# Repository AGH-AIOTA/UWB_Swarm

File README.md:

# UWB Swarm
###### Status - Aktywny
Rój autonomicznych pojazdów na bazie podwozia miabotów, które mogą lokalizować się wzajemnie za pomocą modułów [UWB](https://en.wikipedia.org/wiki/Ultra-wideband).
Projekt realizowany jest w ramach grantu [IDUB](https://www.idub.agh.edu.pl/).

_Niech żyje rój!_

### Założenia/Cel
Wykonanie pojazdów mogących lokalizować się wzajemnie i wykonywać czynności autonomicznie.

### Koordynator
**Wiktor Onik**

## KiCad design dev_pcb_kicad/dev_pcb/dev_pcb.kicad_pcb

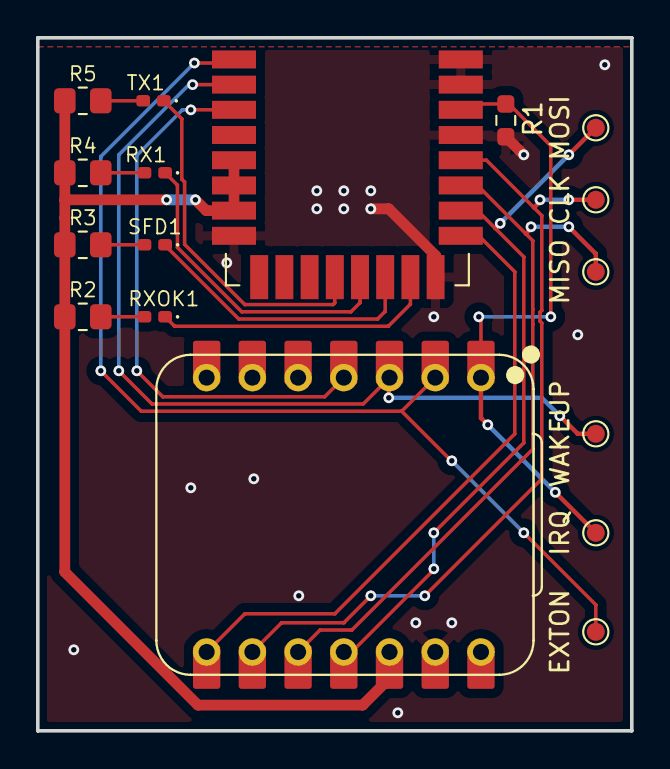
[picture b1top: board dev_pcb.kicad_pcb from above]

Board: 2 copper layers, 33.0 x 38.5 mm, 17 parts (0 on the bottom side), 18 nets.

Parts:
CLK: MISO; TestPoint_Pad_D1.0mm
DWM1: DWM3000; DWM1000
EXTON: TestPoint_Probe; TestPoint_Pad_D1.0mm
IRQ: TestPoint_Probe; TestPoint_Pad_D1.0mm
MISO: CLK; TestPoint_Pad_D1.0mm
MOSI: MOSI; TestPoint_Pad_D1.0mm
R1: 100K; R_0603_1608Metric_Pad0.98x0.95mm_HandSolder
R2, R3, R4, R5: 200; R_0805_2012Metric_Pad1.20x1.40mm_HandSolder
RX1: LED; LED_0402_1005Metric_Pad0.77x0.64mm_HandSolder
RXOK1: LED; LED_0402_1005Metric_Pad0.77x0.64mm_HandSolder
SFD1: LED; LED_0402_1005Metric_Pad0.77x0.64mm_HandSolder
TX1: LED; LED_0402_1005Metric_Pad0.77x0.64mm_HandSolder
U2: XIAO-ESP32-S3-DIP
WAKEUP: TestPoint_Probe; TestPoint_Pad_D1.0mm

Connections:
+3.3V: DWM1.5 (VDDAON), DWM1.6 (VDD3V3), DWM1.7 (VDD3V3), R2.2, R3.2, R4.2, R5.2, U2.12 (3V3)
GND: DWM1.8 (VSS), DWM1.16 (VSS), DWM1.21 (VSS), DWM1.23 (VSS), DWM1.24 (VSS), R1.1, U2.13 (GND)
unnamed: DWM1.1 (EXTON), EXTON.1, U2.2 (GPIO2_A1_D1)
unnamed: DWM1.15 (GPIO0/RXOKLED), RXOK1.1 (K)
unnamed: DWM1.14 (GPIO1/SFDLED), SFD1.1 (K)
unnamed: DWM1.13 (GPIO2/RXLED), RX1.1 (K)
unnamed: DWM1.12 (GPIO3/TXLED), TX1.1 (K)
unnamed: DWM1.22 (IRQ/GPIO8), IRQ.1, R1.2, U2.1 (GPIO1_A0_D0)
unnamed: CLK.1, DWM1.20 (SPICLK), U2.9 (GPIO7_A8_D8_SCK)
unnamed: DWM1.19 (SPIMISO), MISO.1, U2.10 (GPIO8_A9_D9_MISO)
unnamed: DWM1.18 (SPIMOSI), MOSI.1, U2.11 (GPIO9_A10_D10_MOSI)
unnamed: DWM1.2 (WAKEUP), U2.3 (GPIO3_A2_D2), WAKEUP.1
unnamed: DWM1.3 (~RST), U2.4 (GPIO4_A3_D3)
unnamed: DWM1.17 (~SPICS), U2.8 (GPIO44_D7_RX)
unnamed: R4.1, RX1.2 (A)
unnamed: R2.1, RXOK1.2 (A)
unnamed: R3.1, SFD1.2 (A)
unnamed: R5.1, TX1.2 (A)

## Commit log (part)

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2026-03-10 mk1 pcb
2026-03-12 small tracing fixes
2026-03-17 probe points
2026-04-13 Added code for basic single sided twr
2026-06-18 Added documentation for pcb and ss-twr
